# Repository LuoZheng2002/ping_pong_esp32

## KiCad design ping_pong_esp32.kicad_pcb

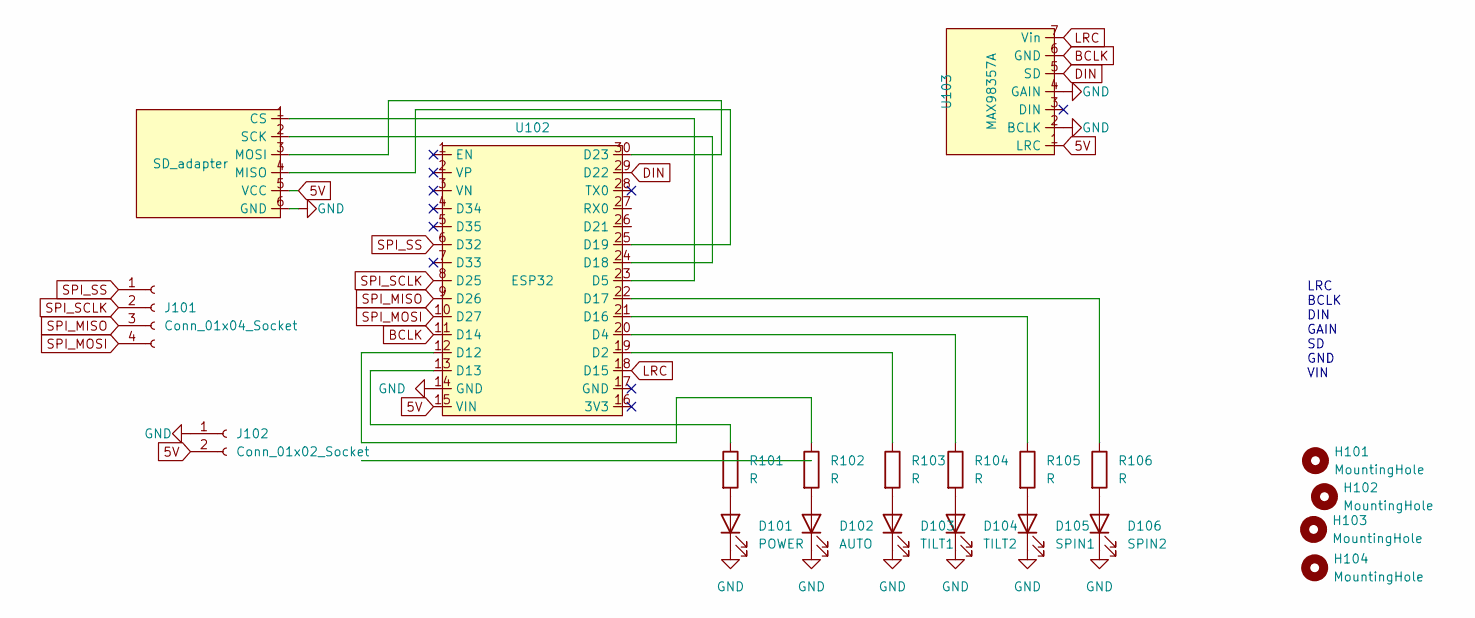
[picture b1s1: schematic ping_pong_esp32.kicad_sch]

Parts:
D101: POWER; LED_D5.0mm
D102: AUTO; LED_D5.0mm
D103: TILT1; LED_D5.0mm
D104: TILT2; LED_D5.0mm
D105: SPIN1; LED_D5.0mm
D106: SPIN2; LED_D5.0mm
H101, H102, H103, H104: MountingHole; MountingHole_3.2mm_M3
J101: Conn_01x04_Socket; PinSocket_1x04_P2.54mm_Vertical
J102: Conn_01x02_Socket; PinSocket_1x02_P2.54mm_Vertical
R101, R102, R103, R104, R105, R106: R; My7.62mmResistor
U101: SD_adapter; SD_Adapter
U102: ESP32; ESP32_30PIN
U103: MAX98357A

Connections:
5V: J102.2, U101.5 (VCC), U102.15 (VIN), U103.1 (LRC)
BCLK: U102.11 (D14), U103.6 (GND)
DIN: U102.29 (D22), U103.5 (SD)
GND: D101.1 (K), D102.1 (K), D103.1 (K), D104.1 (K), D105.1 (K), D106.1 (K), J102.1, U101.6 (GND), U102.14 (GND), U103.2 (BCLK), U103.4 (GAIN)
LRC: U102.18 (D15), U103.7 (Vin)
unnamed: D101.2 (A), R101.2
unnamed: D102.2 (A), R102.2
unnamed: D103.2 (A), R103.2
unnamed: D104.2 (A), R104.2
unnamed: D105.2 (A), R105.2
unnamed: D106.2 (A), R106.2
unnamed: U101.1 (CS), U102.23 (D5)
unnamed: U101.4 (MISO), U102.25 (D19)
unnamed: U101.3 (MOSI), U102.30 (D23)
unnamed: U101.2 (SCK), U102.24 (D18)
unnamed: R103.1, U102.19 (D2)
unnamed: R104.1, U102.20 (D4)
unnamed: R102.1, U102.12 (D12)
unnamed: R101.1, U102.13 (D13)
unnamed: R105.1, U102.21 (D16)
unnamed: R106.1, U102.22 (D17)
SPI_MISO: J101.3, U102.9 (D26)
SPI_MOSI: J101.4, U102.10 (D27)
SPI_SCLK: J101.2, U102.8 (D25)
SPI_SS: J101.1, U102.6 (D32)

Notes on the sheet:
LRC BCLK DIN GAIN SD GND VIN

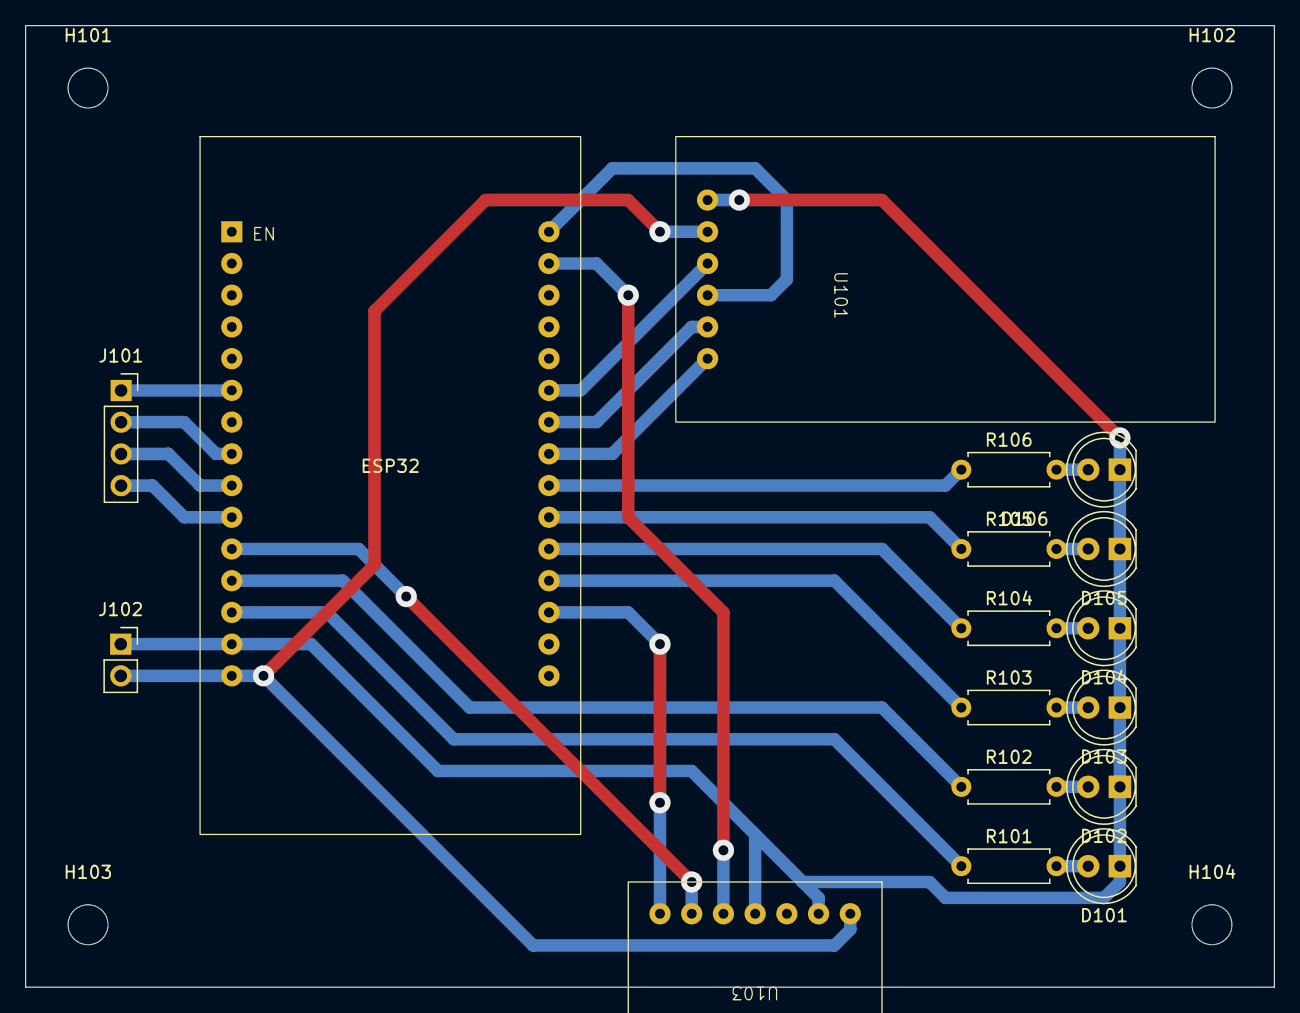
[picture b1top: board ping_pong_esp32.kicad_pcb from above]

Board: 2 copper layers, 100.0 x 77.0 mm, 21 parts (0 on the bottom side), 25 nets.

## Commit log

2024-04-22 checkpoint
